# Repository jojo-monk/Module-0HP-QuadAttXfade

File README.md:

# Module-0HP-QuadAttXfade
Quadruple attenuateur passif
Testé et Fonctionnel

2 petites erreurs de cablage :
- le potentiometre Mix out que j'ai cablé à l'envers, ainsi que le bouton mute du Mix out.

  Ces erreurs ont été corrigés dans le fichier kicad, et les fichiers gerber.
  Comme je m'en suisapeçu après fabrication, j'ai juste refait une étiquette pour corriger la serigraphie.

2 small wiring errors:
- the Mix out potentiometer that I wired backwards, as well as the Mix out mute button.

   These errors have been corrected in the kicad file, and the gerber files.
   As I noticed after manufacturing, I just made a label again to correct the screen printing.

[Build document](https://htmlpreview.github.io/?https://github.com/jojo-monk/Module-0HP-QuadAttXfade/blob/main/ibom.html)

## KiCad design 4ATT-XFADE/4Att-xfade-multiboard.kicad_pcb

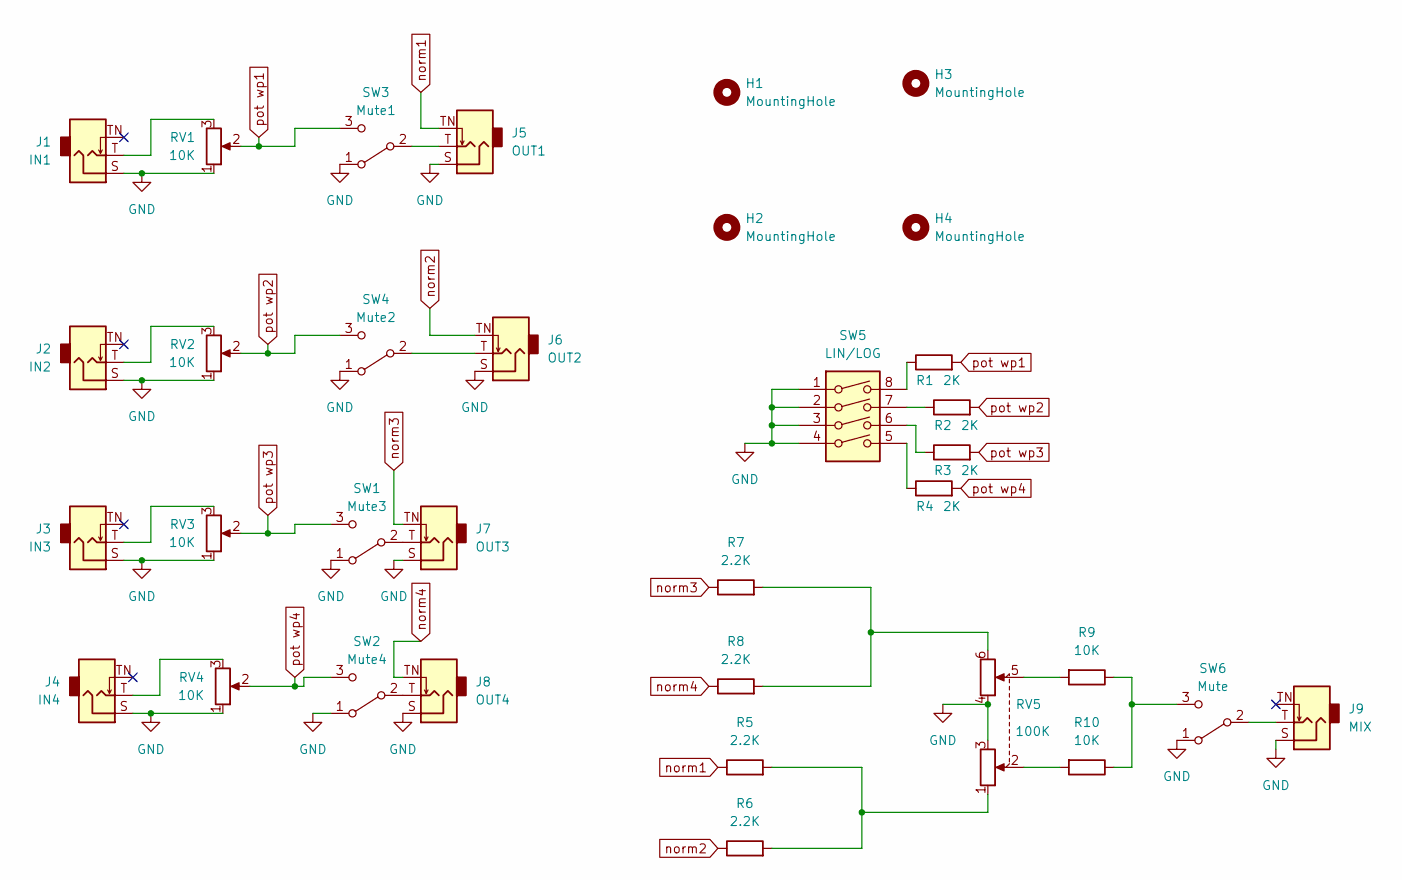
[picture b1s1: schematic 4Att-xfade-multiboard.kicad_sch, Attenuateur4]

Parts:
H1, H2, H3, H4: MountingHole; MountingHole_3.2mm_M3
J1: IN1; Jack_3.5mm_QingPu_WQP-PJ301M-12_Vertical
J2: IN2; Jack_3.5mm_QingPu_WQP-PJ301M-12_Vertical
J3: IN3; Jack_3.5mm_QingPu_WQP-PJ301M-12_Vertical
J4: IN4; Jack_3.5mm_QingPu_WQP-PJ301M-12_Vertical
J5: OUT1; Jack_3.5mm_QingPu_WQP-PJ301M-12_Vertical
J6: OUT2; Jack_3.5mm_QingPu_WQP-PJ301M-12_Vertical
J7: OUT3; Jack_3.5mm_QingPu_WQP-PJ301M-12_Vertical
J8: OUT4; Jack_3.5mm_QingPu_WQP-PJ301M-12_Vertical
J9: MIX; Jack_3.5mm_QingPu_WQP-PJ301M-12_Vertical
R1, R2, R3, R4: 2K; R_Axial_DIN0207_L6.3mm_D2.5mm_P10.16mm_Horizontal
R5, R6, R7, R8: 2.2K; R_Axial_DIN0207_L6.3mm_D2.5mm_P10.16mm_Horizontal
R9, R10: 10K; R_Axial_DIN0207_L6.3mm_D2.5mm_P10.16mm_Horizontal
RV1, RV2, RV3, RV4: 10K; Potentiometer_Alpha_RD901F-40-00D_Single_Vertical
RV5: 100K; Potentiometer_Alpha_RD902F-40-00D_Dual_Vertical
SW1: Mute3; Switch_Toggle_SPDT_Mini_SolderLug
SW2: Mute4; Switch_Toggle_SPDT_Mini_SolderLug
SW3: Mute1; Switch_Toggle_SPDT_Mini_SolderLug
SW4: Mute2; Switch_Toggle_SPDT_Mini_SolderLug
SW5: LIN/LOG; SW_DIP_SPSTx04_Slide_9.78x12.34mm_W7.62mm_P2.54mm
SW6: Mute; Switch_Toggle_SPDT_Mini_SolderLug

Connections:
GND: J1.S, J2.S, J3.S, J4.S, J5.S, J6.S, J7.S, J8.S, J9.S, RV1.1, RV2.1, RV3.1, RV4.1, RV5.3, RV5.4, SW1.1 (A), SW2.1 (A), SW3.1 (A), SW4.1 (A), SW5.1, SW5.2, SW5.3, SW5.4, SW6.1 (A)
unnamed: J1.T, RV1.3
unnamed: J2.T, RV2.3
unnamed: J3.T, RV3.3
unnamed: J4.T, RV4.3
unnamed: J5.T, SW3.2 (B)
unnamed: J6.T, SW4.2 (B)
unnamed: J7.T, SW1.2 (B)
unnamed: J8.T, SW2.2 (B)
unnamed: J9.T, SW6.2 (B)
unnamed: R1.1, SW5.8
unnamed: R2.1, SW5.7
unnamed: R3.1, SW5.6
unnamed: R4.1, SW5.5
unnamed: R5.2, R6.2, RV5.1
unnamed: R7.2, R8.2, RV5.6
unnamed: R9.2, RV5.5
unnamed: R9.1, R10.1, SW6.3 (C)
unnamed: R10.2, RV5.2
norm1: J5.TN, R5.1
norm2: J6.TN, R6.1
norm3: J7.TN, R7.1
norm4: J8.TN, R8.1
pot wp1: R1.2, RV1.2, SW3.3 (C)
pot wp2: R2.2, RV2.2, SW4.3 (C)
pot wp3: R3.2, RV3.2, SW1.3 (C)
pot wp4: R4.2, RV4.2, SW2.3 (C)

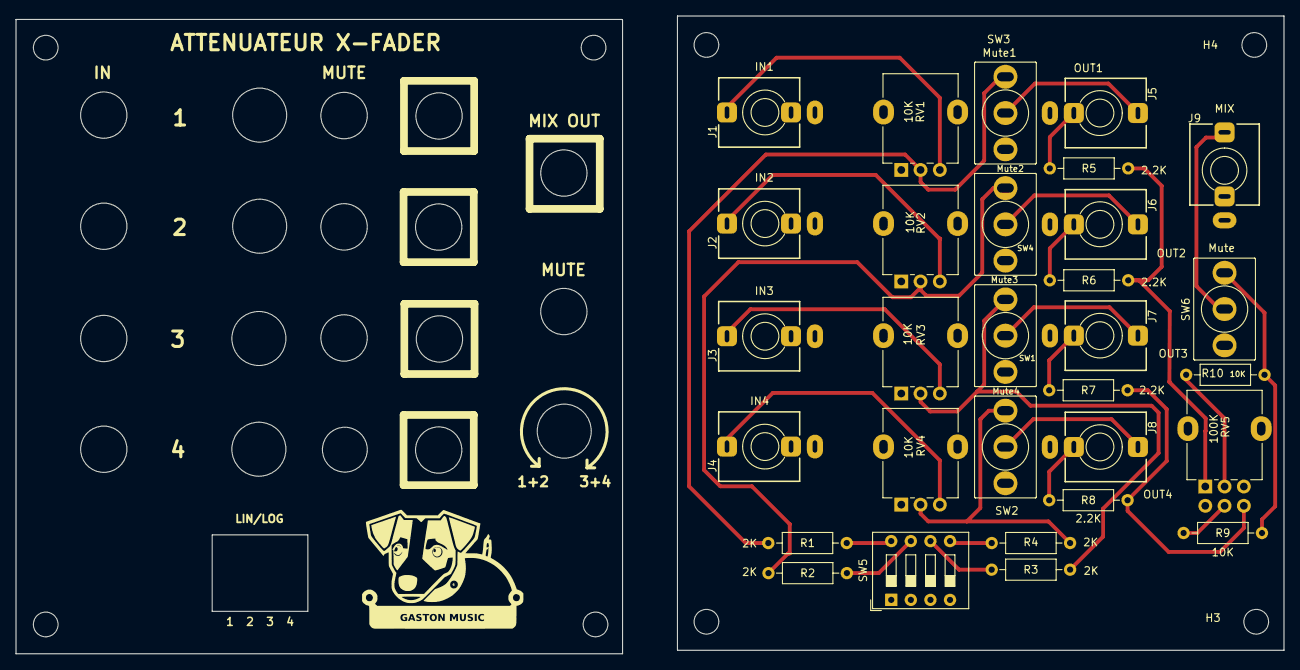
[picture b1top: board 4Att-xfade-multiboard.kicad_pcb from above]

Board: 2 copper layers, 78.6 x 82.2 mm, 34 parts (0 on the bottom side), 27 nets.

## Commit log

2023-08-31 fabrication
2023-08-31 ajout ibom
2023-09-01 correction Mute
2023-09-15 ajout image
